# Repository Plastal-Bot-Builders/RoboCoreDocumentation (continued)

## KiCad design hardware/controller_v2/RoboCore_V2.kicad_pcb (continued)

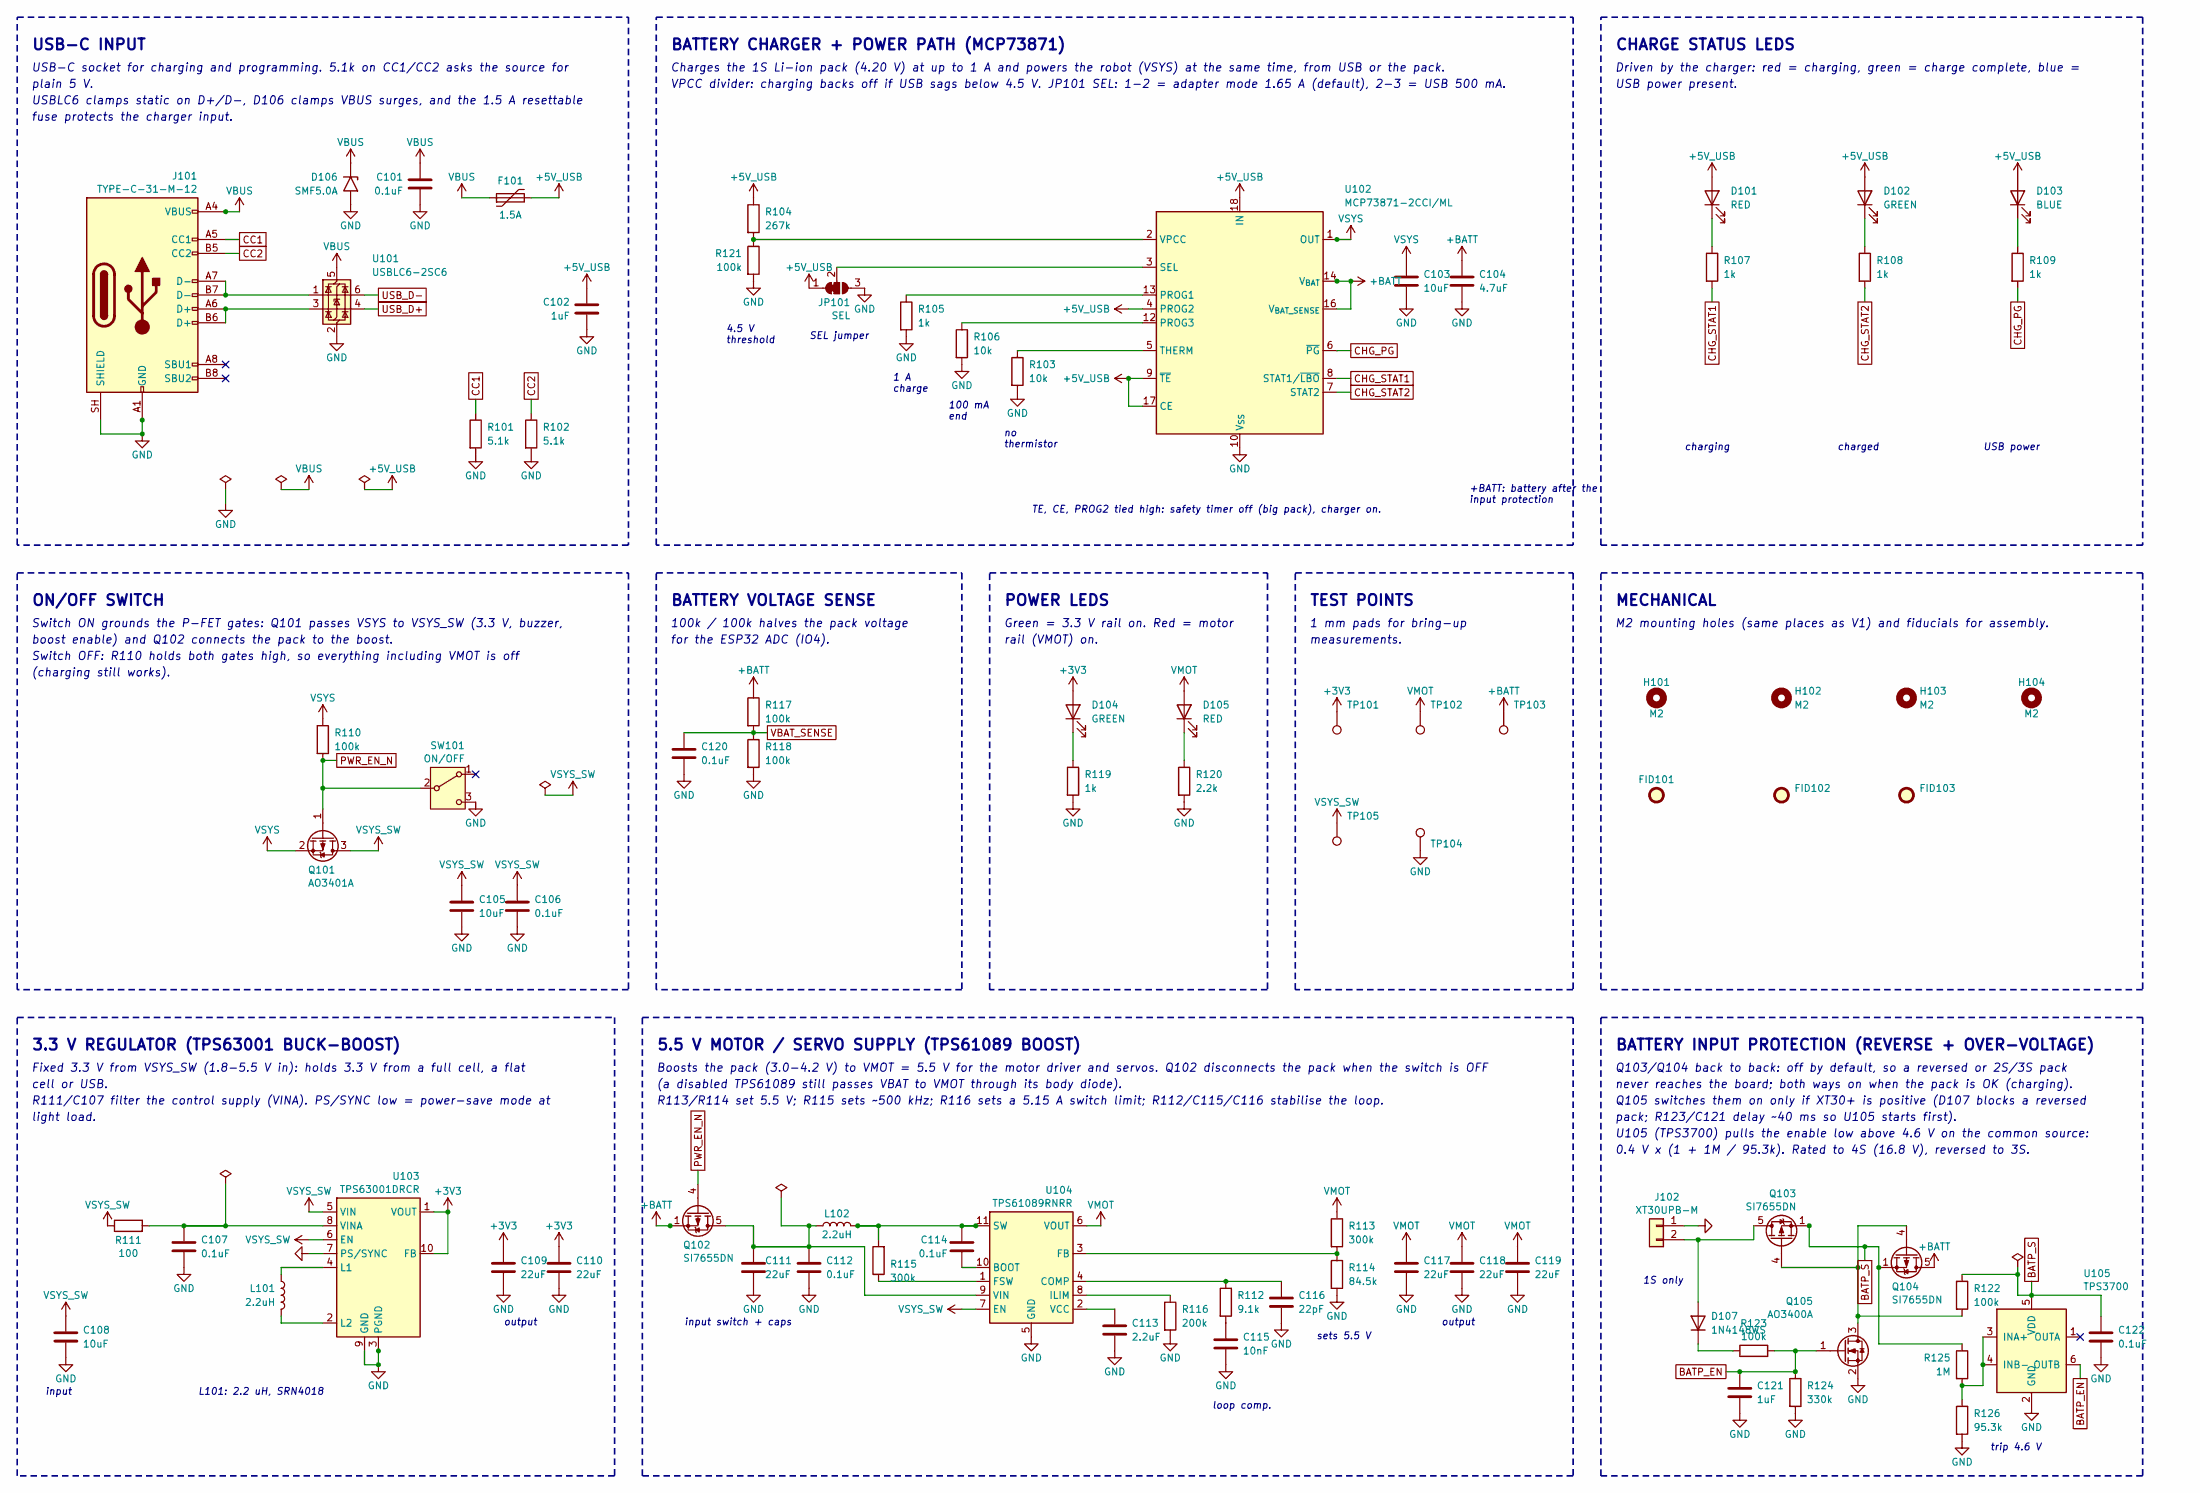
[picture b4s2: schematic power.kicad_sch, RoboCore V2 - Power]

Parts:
C101, C106, C107, C112, C114, C120, C122: 0.1uF; C_0402_1005Metric; LCSC C960916
C102: 1uF; C_0603_1608Metric; LCSC C5673
C103: 10uF; C_0603_1608Metric; LCSC C92487
C104: 4.7uF; C_0805_2012Metric; LCSC C1779
C105, C108: 10uF; C_0805_2012Metric; LCSC C1713
C109, C110: 22uF; C_0805_2012Metric; LCSC C45783
C111, C117, C118, C119: 22uF; C_1206_3216Metric; LCSC C12891
C113: 2.2uF; C_0603_1608Metric; LCSC C23630
C115: 10nF; C_0402_1005Metric; LCSC C15195
C116: 22pF; C_0402_1005Metric; LCSC C70464
C121: 1uF; C_0402_1005Metric; LCSC C16193167
D101, D105: RED; LED_0603_1608Metric; LCSC C125099
D102, D104: GREEN; LED_0603_1608Metric; LCSC C125098
D103: BLUE; LED_0603_1608Metric; LCSC C99290
D106: SMF5.0A; D_SMF; LCSC C151296
D107: 1N4148WS; D_SOD-323; LCSC C129905
F101: 1.5A; Fuse_1812_4532Metric; LCSC C78695
FID101, FID102, FID103: Fiducial; Fiducial_1mm_Mask2mm
H101, H102, H103, H104: M2; MountingHole_2.2mm_M2
J101: TYPE-C-31-M-12; USB_C_Receptacle_HRO_TYPE-C-31-M-12; LCSC C165948
J102: XT30UPB-M; AMASS_XT30UPB-M_1x02_P5.0mm_Vertical; LCSC C428721
JP101: SEL; SolderJumper-3_P1.3mm_Bridged12_RoundedPad1.0x1.5mm
L101: 2.2uH; L_Bourns-SRN4018; LCSC C913207
L102: 2.2uH; L_Bourns_SRP5030CA; LCSC C2046809
Q101: AO3401A; SOT-23; LCSC C15127
Q102, Q103, Q104: SI7655DN; Vishay_PowerPAK_1212-8_Single; LCSC C727830
Q105: AO3400A; SOT-23; LCSC C20917
R101, R102: 5.1k; R_0402_1005Metric; LCSC C25905
R103, R106: 10k; R_0402_1005Metric; LCSC C25744
R104: 267k; R_0402_1005Metric; LCSC C270622
R105, R107, R108, R109, R119: 1k; R_0402_1005Metric; LCSC C106235
R110, R117, R118, R121, R122, R123: 100k; R_0402_1005Metric; LCSC C25741
R111: 100; R_0402_1005Metric; LCSC C106232
R112: 9.1k; R_0402_1005Metric; LCSC C25926
R113, R115: 300k; R_0402_1005Metric; LCSC C25774
R114: 84.5k; R_0402_1005Metric; LCSC C26988
R116: 200k; R_0402_1005Metric; LCSC C25764
R120: 2.2k; R_0402_1005Metric; LCSC C25879
R124: 330k; R_0402_1005Metric; LCSC C25778
R125: 1M; R_0402_1005Metric; LCSC C26083
R126: 95.3k; R_0402_1005Metric; LCSC C26990
SW101: ON/OFF; SW_SPDT_CK_JS102011SAQN; LCSC C221660
TP101: +3V3; TestPoint_Pad_D1.0mm
TP102: VMOT; TestPoint_Pad_D1.0mm
TP103: +BATT; TestPoint_Pad_D1.0mm
TP104: GND; TestPoint_Pad_D1.0mm
TP105: VSYS_SW; TestPoint_Pad_D1.0mm
U101: USBLC6-2SC6; SOT-23-6; LCSC C7519
U102: MCP73871-2CCI/ML; QFN-20-1EP_4x4mm_P0.5mm_EP2.5x2.5mm_ThermalVias; LCSC C5121473
U103: TPS63001DRCR; Texas_DRC0010J_ThermalVias; LCSC C28060
U104: TPS61089RNRR; Texas_VQFN-RNR0011A-11; LCSC C165129
U105: TPS3700; TSOT-23-6; LCSC C33002

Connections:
+3V3: C109.1, C110.1, D104.2 (A), TP101.1, U103.1 (VOUT), U103.10 (FB); also elsewhere on the board
+5V_USB: C102.1, D101.2 (A), D102.2 (A), D103.2 (A), F101.2, JP101.1 (A), R104.1, U102.4 (PROG2), U102.9 (~TE), U102.17 (CE), U102.18 (IN), U102.19 (IN)
+BATT: C104.1, Q102.1 (S), Q102.2 (S), Q102.3 (S), Q104.5 (D), R117.1, TP103.1, U102.14 (V_{BAT}), U102.15 (V_{BAT}), U102.16 (V_{BAT_SENSE})
BATP_EN: C121.1, Q105.1 (G), R123.2, R124.1, U105.6 (OUTB)
BATP_S: C122.1, Q103.1 (S), Q103.2 (S), Q103.3 (S), Q104.1 (S), Q104.2 (S), Q104.3 (S), R122.1, R125.1, U105.5 (VDD)
CC1: J101.A5 (CC1), R101.1
CC2: J101.B5 (CC2), R102.1
CHG_PG: R109.2, U102.6 (~PG)
CHG_STAT1: R107.2, U102.8 (STAT1/~LBO)
CHG_STAT2: R108.2, U102.7 (STAT2)
GND: C101.2, C102.2, C103.2, C104.2, C105.2, C106.2, C107.2, C108.2, C109.2, C110.2, C111.2, C112.2, C113.2, C115.2, C116.2, C117.2, C118.2, C119.2, C120.2, C121.2, C122.2, D106.2 (A2), J101.A1 (GND), J101.A12 (GND), J101.B1 (GND), J101.B12 (GND), J101.SH (SHIELD), J102.1, JP101.3 (B), Q105.2 (S), R101.2, R102.2, R103.2, R105.2, R106.2, R114.2, R116.2, R118.2, R119.2, R120.2, R121.2, R124.2, R126.2, SW101.3 (C), TP104.1, U101.2 (GND), U102.10 (V_{SS}), U102.11 (V_{SS}), U102.21 (V_{SS}), U103.3 (PGND), U103.7 (PS/SYNC), U103.9 (GND), U103.11 (PGND), U104.5 (GND), U105.2 (GND); also elsewhere on the board
unnamed: C115.1, R112.2
unnamed: D101.1 (K), R107.1
unnamed: D102.1 (K), R108.1
unnamed: D103.1 (K), R109.1
unnamed: D104.1 (K), R119.1
unnamed: D105.1 (K), R120.1
unnamed: D107.2 (A), J102.2, Q103.5 (D)
unnamed: D107.1 (K), R123.1
unnamed: J101.A6 (D+), J101.B6 (D+), U101.3 (I/O2)
unnamed: J101.A7 (D-), J101.B7 (D-), U101.1 (I/O1)
unnamed: JP101.2 (C), U102.3 (SEL)
unnamed: C111.1, C112.1, L102.1, Q102.5 (D), U104.9 (VIN)
unnamed: Q103.4 (G), Q104.4 (G), Q105.3 (D), R122.2
unnamed: R105.1, U102.13 (PROG1)
unnamed: R106.1, U102.12 (PROG3)
unnamed: R103.1, U102.5 (THERM)
unnamed: R104.2, R121.1, U102.2 (VPCC)
unnamed: L101.1, U103.4 (L1)
unnamed: L101.2, U103.2 (L2)
unnamed: C107.1, R111.2, U103.8 (VINA)
unnamed: C114.1, U104.10 (BOOT)
unnamed: C116.1, R112.1, U104.4 (COMP)
unnamed: R113.2, R114.1, U104.3 (FB)
unnamed: R115.1, U104.1 (FSW)
unnamed: R116.1, U104.8 (ILIM)
unnamed: C114.2, L102.2, R115.2, U104.11 (SW)
unnamed: C113.1, U104.2 (VCC)
unnamed: R125.2, R126.1, U105.3 (INA+), U105.4 (INB-)
PWR_EN_N: Q101.1 (G), Q102.4 (G), R110.2, SW101.2 (B)
USB_D+: U101.4 (I/O2); also elsewhere on the board
USB_D-: U101.6 (I/O1); also elsewhere on the board
VBAT_SENSE: C120.1, R117.2, R118.1; also elsewhere on the board
VBUS: C101.1, D106.1 (A1), F101.1, J101.A4 (VBUS), J101.A9 (VBUS), J101.B4 (VBUS), J101.B9 (VBUS), U101.5 (VBUS)
VMOT: C117.1, C118.1, C119.1, D105.2 (A), R113.1, TP102.1, U104.6 (VOUT); also elsewhere on the board
VSYS: C103.1, Q101.2 (S), R110.1, U102.1 (OUT), U102.20 (OUT)
VSYS_SW: C105.1, C106.1, C108.1, Q101.3 (D), R111.1, TP105.1, U103.5 (VIN), U103.6 (EN), U104.7 (EN); also elsewhere on the board

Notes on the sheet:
USB-C INPUT
USB-C socket for charging and programming. 5.1k on CC1/CC2 asks the source for
plain 5 V.
USBLC6 clamps static on D+/D-, D106 clamps VBUS surges, and the 1.5 A resettable
fuse protects the charger input.
BATTERY CHARGER + POWER PATH (MCP73871)
Charges the 1S Li-ion pack (4.20 V) at up to 1 A and powers the robot (VSYS) at the same time, from USB or the pack.
VPCC divider: charging backs off if USB sags below 4.5 V. JP101 SEL: 1-2 = adapter mode 1.65 A (default), 2-3 = USB 500 mA.
4.5 V
threshold
SEL jumper
1 A
charge
100 mA
end
thermistor
TE, CE, PROG2 tied high: safety timer off (big pack), charger on.
+BATT: battery after the
input protection
CHARGE STATUS LEDS
Driven by the charger: red = charging, green = charge complete, blue =
USB power present.
charging
charged
USB power
ON/OFF SWITCH
Switch ON grounds the P-FET gates: Q101 passes VSYS to VSYS_SW (3.3 V, buzzer,
boost enable) and Q102 connects the pack to the boost.
Switch OFF: R110 holds both gates high, so everything including VMOT is off
(charging still works).
BATTERY VOLTAGE SENSE
100k / 100k halves the pack voltage
for the ESP32 ADC (IO4).
POWER LEDS
Green = 3.3 V rail on. Red = motor
rail (VMOT) on.
TEST POINTS
1 mm pads for bring-up
measurements.
MECHANICAL

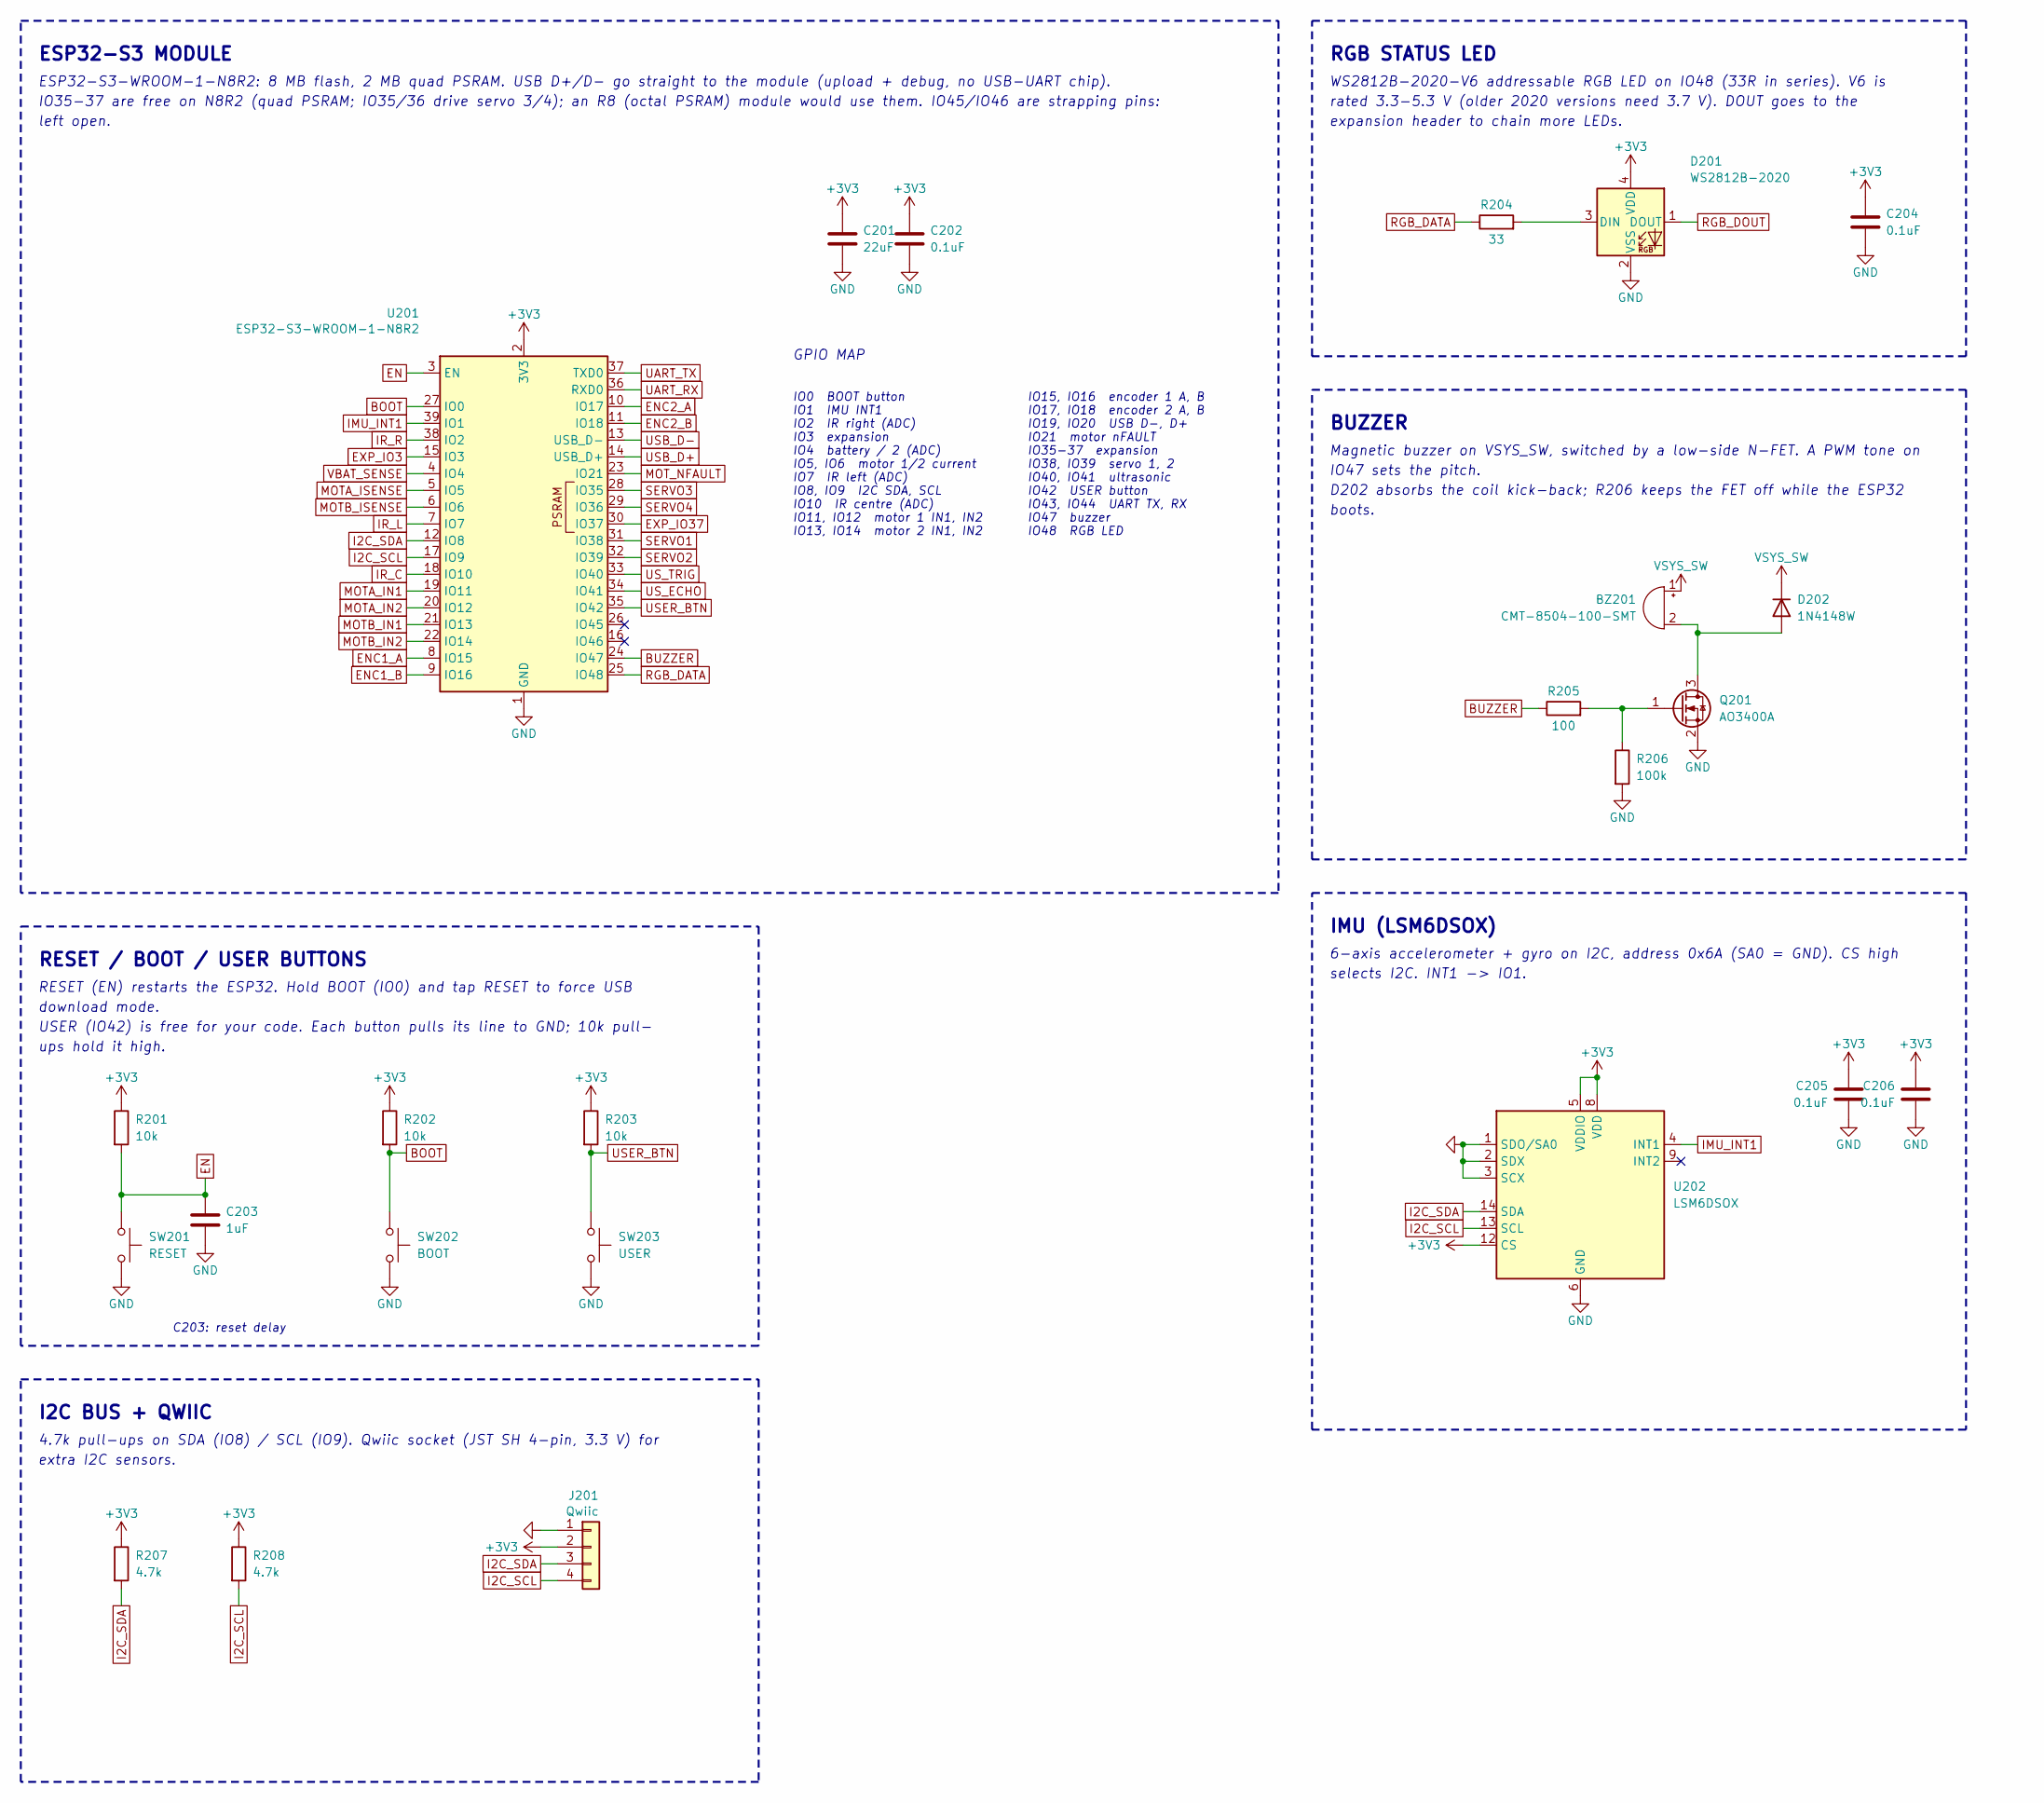
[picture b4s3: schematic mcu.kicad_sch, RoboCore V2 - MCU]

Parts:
BZ201: CMT-8504-100-SMT; MagneticBuzzer_CUI_CMT-8504-100-SMT; LCSC C22359707
C201: 22uF; C_0805_2012Metric; LCSC C45783
C202, C204, C205, C206: 0.1uF; C_0402_1005Metric; LCSC C960916
C203: 1uF; C_0402_1005Metric; LCSC C16193167
D201: WS2812B-2020; LED_WS2812B-2020_PLCC4_2.0x2.0mm; LCSC C52917434
D202: 1N4148W; D_SOD-123; LCSC C83528
J201: Qwiic; JST_SH_BM04B-SRSS-TB_1x04-1MP_P1.00mm_Vertical; LCSC C160390
Q201: AO3400A; SOT-23; LCSC C20917
R201, R202, R203: 10k; R_0402_1005Metric; LCSC C25744
R204: 33; R_0402_1005Metric; LCSC C138002
R205: 100; R_0402_1005Metric; LCSC C106232
R206: 100k; R_0402_1005Metric; LCSC C25741
R207, R208: 4.7k; R_0402_1005Metric; LCSC C25900
SW201: RESET; SW_SPST_SKQG_WithoutStem; LCSC C116647
SW202: BOOT; SW_SPST_SKQG_WithoutStem; LCSC C116647
SW203: USER; SW_SPST_SKQG_WithoutStem; LCSC C116647
U201: ESP32-S3-WROOM-1-N8R2; ESP32-S3-WROOM-1; LCSC C2913204
U202: LSM6DSOX; LGA-14_3x2.5mm_P0.5mm_LayoutBorder3x4y; LCSC C481766

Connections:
+3V3: C201.1, C202.1, C204.1, C205.1, C206.1, D201.4 (VDD), J201.2, R201.1, R202.1, R203.1, R207.1, R208.1, U201.2 (3V3), U202.5 (VDDIO), U202.8 (VDD), U202.12 (CS); also elsewhere on the board
BOOT: R202.2, SW202.1, U201.27 (IO0)
BUZZER: R205.1, U201.24 (IO47); also elsewhere on the board
EN: C203.1, R201.2, SW201.1, U201.3 (EN); also elsewhere on the board
ENC1_A: U201.8 (IO15); also elsewhere on the board
ENC1_B: U201.9 (IO16); also elsewhere on the board
ENC2_A: U201.10 (IO17); also elsewhere on the board
ENC2_B: U201.11 (IO18); also elsewhere on the board
EXP_IO3: U201.15 (IO3); also elsewhere on the board
EXP_IO37: U201.30 (IO37); also elsewhere on the board
GND: C201.2, C202.2, C203.2, C204.2, C205.2, C206.2, D201.2 (VSS), J201.1, Q201.2 (S), R206.2, SW201.2, SW202.2, SW203.2, U201.1 (GND), U201.40 (GND), U201.41 (GND), U202.1 (SDO/SA0), U202.2 (SDX), U202.3 (SCX), U202.6 (GND), U202.7 (GND); also elsewhere on the board
I2C_SCL: J201.4, R208.2, U201.17 (IO9), U202.13 (SCL); also elsewhere on the board
I2C_SDA: J201.3, R207.2, U201.12 (IO8), U202.14 (SDA); also elsewhere on the board
IMU_INT1: U201.39 (IO1), U202.4 (INT1); also elsewhere on the board
IR_C: U201.18 (IO10); also elsewhere on the board
IR_L: U201.7 (IO7); also elsewhere on the board
IR_R: U201.38 (IO2); also elsewhere on the board
MOTA_IN1: U201.19 (IO11); also elsewhere on the board
MOTA_IN2: U201.20 (IO12); also elsewhere on the board
MOTA_ISENSE: U201.5 (IO5); also elsewhere on the board
MOTB_IN1: U201.21 (IO13); also elsewhere on the board
MOTB_IN2: U201.22 (IO14); also elsewhere on the board
MOTB_ISENSE: U201.6 (IO6); also elsewhere on the board
MOT_NFAULT: U201.23 (IO21); also elsewhere on the board
unnamed: BZ201.2 (-), D202.2 (A), Q201.3 (D)
unnamed: D201.3 (DIN), R204.2
unnamed: Q201.1 (G), R205.2, R206.1
RGB_DATA: R204.1, U201.25 (IO48)
RGB_DOUT: D201.1 (DOUT); also elsewhere on the board
SERVO1: U201.31 (IO38); also elsewhere on the board
SERVO2: U201.32 (IO39); also elsewhere on the board
SERVO3: U201.28 (IO35); also elsewhere on the board
SERVO4: U201.29 (IO36); also elsewhere on the board
UART_RX: U201.36 (RXD0); also elsewhere on the board
UART_TX: U201.37 (TXD0); also elsewhere on the board
USB_D+: U201.14 (USB_D+); also elsewhere on the board
USB_D-: U201.13 (USB_D-); also elsewhere on the board
USER_BTN: R203.2, SW203.1, U201.35 (IO42); also elsewhere on the board
US_ECHO: U201.34 (IO41); also elsewhere on the board
US_TRIG: U201.33 (IO40); also elsewhere on the board
VBAT_SENSE: U201.4 (IO4); also elsewhere on the board
VSYS_SW: BZ201.1 (+), D202.1 (K); also elsewhere on the board

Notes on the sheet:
ESP32-S3 MODULE
ESP32-S3-WROOM-1-N8R2: 8 MB flash, 2 MB quad PSRAM. USB D+/D- go straight to the module (upload + debug, no USB-UART chip).
IO35-37 are free on N8R2 (quad PSRAM; IO35/36 drive servo 3/4); an R8 (octal PSRAM) module would use them. IO45/IO46 are strapping pins:
left open.
GPIO MAP
IO0 BOOT button
IO1 IMU INT1
IO2 IR right (ADC)
IO3 expansion
IO4 battery / 2 (ADC)
IO5, IO6 motor 1/2 current
IO7 IR left (ADC)
IO8, IO9 I2C SDA, SCL
IO10 IR centre (ADC)
IO11, IO12 motor 1 IN1, IN2
IO13, IO14 motor 2 IN1, IN2
IO15, IO16 encoder 1 A, B
IO17, IO18 encoder 2 A, B
IO19, IO20 USB D-, D+
IO21 motor nFAULT
IO35-37 expansion
IO38, IO39 servo 1, 2
IO40, IO41 ultrasonic
IO42 USER button
IO43, IO44 UART TX, RX
IO47 buzzer
IO48 RGB LED
RESET / BOOT / USER BUTTONS
RESET (EN) restarts the ESP32. Hold BOOT (IO0) and tap RESET to force USB
download mode.
USER (IO42) is free for your code. Each button pulls its line to GND; 10k pull-
ups hold it high.
C203: reset delay
I2C BUS + QWIIC
4.7k pull-ups on SDA (IO8) / SCL (IO9). Qwiic socket (JST SH 4-pin, 3.3 V) for
extra I2C sensors.
RGB STATUS LED
WS2812B-2020-V6 addressable RGB LED on IO48 (33R in series). V6 is
rated 3.3-5.3 V (older 2020 versions need 3.7 V). DOUT goes to the
expansion header to chain more LEDs.

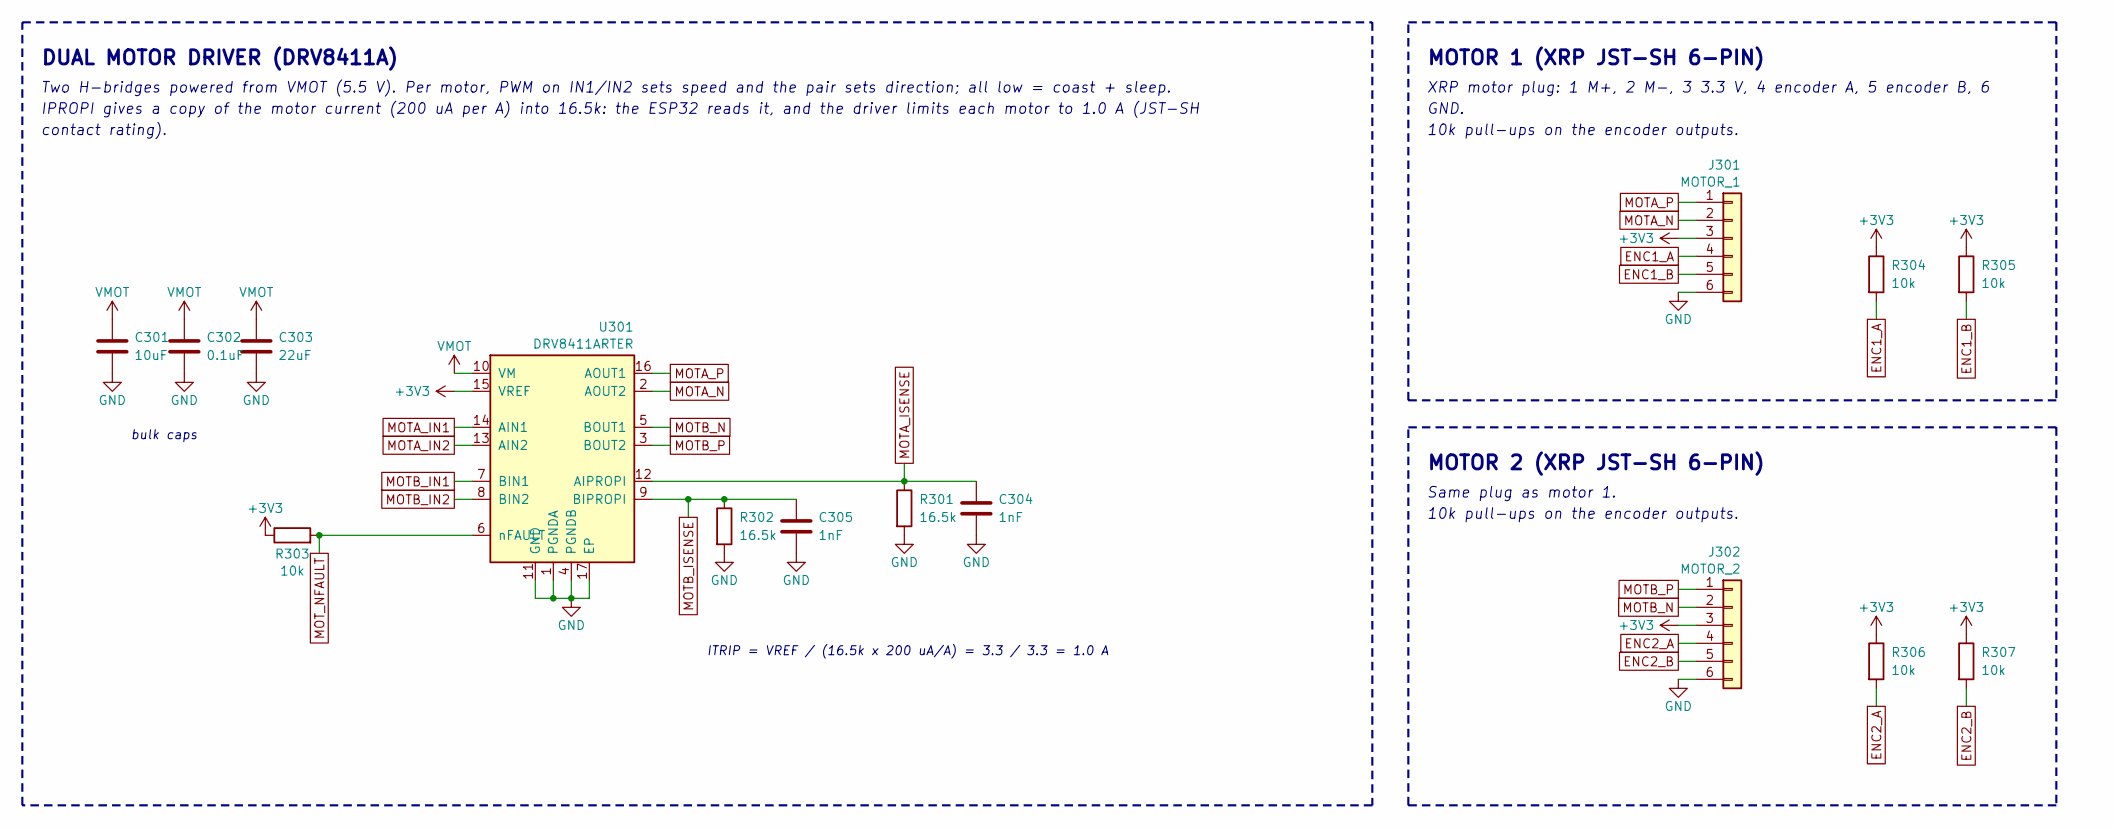
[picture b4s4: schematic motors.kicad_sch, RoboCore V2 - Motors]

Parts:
C301: 10uF; C_0805_2012Metric; LCSC C1713
C302: 0.1uF; C_0402_1005Metric; LCSC C960916
C303: 22uF; C_1206_3216Metric; LCSC C12891
C304, C305: 1nF; C_0402_1005Metric; LCSC C14442
J301: MOTOR_1; JST_SH_BM06B-SRSS-TB_1x06-1MP_P1.00mm_Vertical; LCSC C160392
J302: MOTOR_2; JST_SH_BM06B-SRSS-TB_1x06-1MP_P1.00mm_Vertical; LCSC C160392
R301, R302: 16.5k; R_0402_1005Metric; LCSC C25857
R303, R304, R305, R306, R307: 10k; R_0402_1005Metric; LCSC C25744
U301: DRV8411ARTER; WQFN-16-1EP_3x3mm_P0.5mm_EP1.68x1.68mm_ThermalVias; LCSC C18816315

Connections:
+3V3: J301.3, J302.3, R303.1, R304.1, R305.1, R306.1, R307.1, U301.15 (VREF); also elsewhere on the board
ENC1_A: J301.4, R304.2; also elsewhere on the board
ENC1_B: J301.5, R305.2; also elsewhere on the board
ENC2_A: J302.4, R306.2; also elsewhere on the board
ENC2_B: J302.5, R307.2; also elsewhere on the board
GND: C301.2, C302.2, C303.2, C304.2, C305.2, J301.6, J302.6, R301.2, R302.2, U301.1 (PGNDA), U301.4 (PGNDB), U301.11 (GND), U301.17 (EP); also elsewhere on the board
MOTA_IN1: U301.14 (AIN1); also elsewhere on the board
MOTA_IN2: U301.13 (AIN2); also elsewhere on the board
MOTA_ISENSE: C304.1, R301.1, U301.12 (AIPROPI); also elsewhere on the board
MOTA_N: J301.2, U301.2 (AOUT2)
MOTA_P: J301.1, U301.16 (AOUT1)
MOTB_IN1: U301.7 (BIN1); also elsewhere on the board
MOTB_IN2: U301.8 (BIN2); also elsewhere on the board
MOTB_ISENSE: C305.1, R302.1, U301.9 (BIPROPI); also elsewhere on the board
MOTB_N: J302.2, U301.5 (BOUT1)
MOTB_P: J302.1, U301.3 (BOUT2)
MOT_NFAULT: R303.2, U301.6 (nFAULT); also elsewhere on the board
VMOT: C301.1, C302.1, C303.1, U301.10 (VM); also elsewhere on the board

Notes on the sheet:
DUAL MOTOR DRIVER (DRV8411A)
Two H-bridges powered from VMOT (5.5 V). Per motor, PWM on IN1/IN2 sets speed and the pair sets direction; all low = coast + sleep.
IPROPI gives a copy of the motor current (200 uA per A) into 16.5k: the ESP32 reads it, and the driver limits each motor to 1.0 A (JST-SH
contact rating).
ITRIP = VREF / (16.5k x 200 uA/A) = 3.3 / 3.3 = 1.0 A
bulk caps
MOTOR 1 (XRP JST-SH 6-PIN)
XRP motor plug: 1 M+, 2 M-, 3 3.3 V, 4 encoder A, 5 encoder B, 6
GND.
10k pull-ups on the encoder outputs.
MOTOR 2 (XRP JST-SH 6-PIN)
Same plug as motor 1.

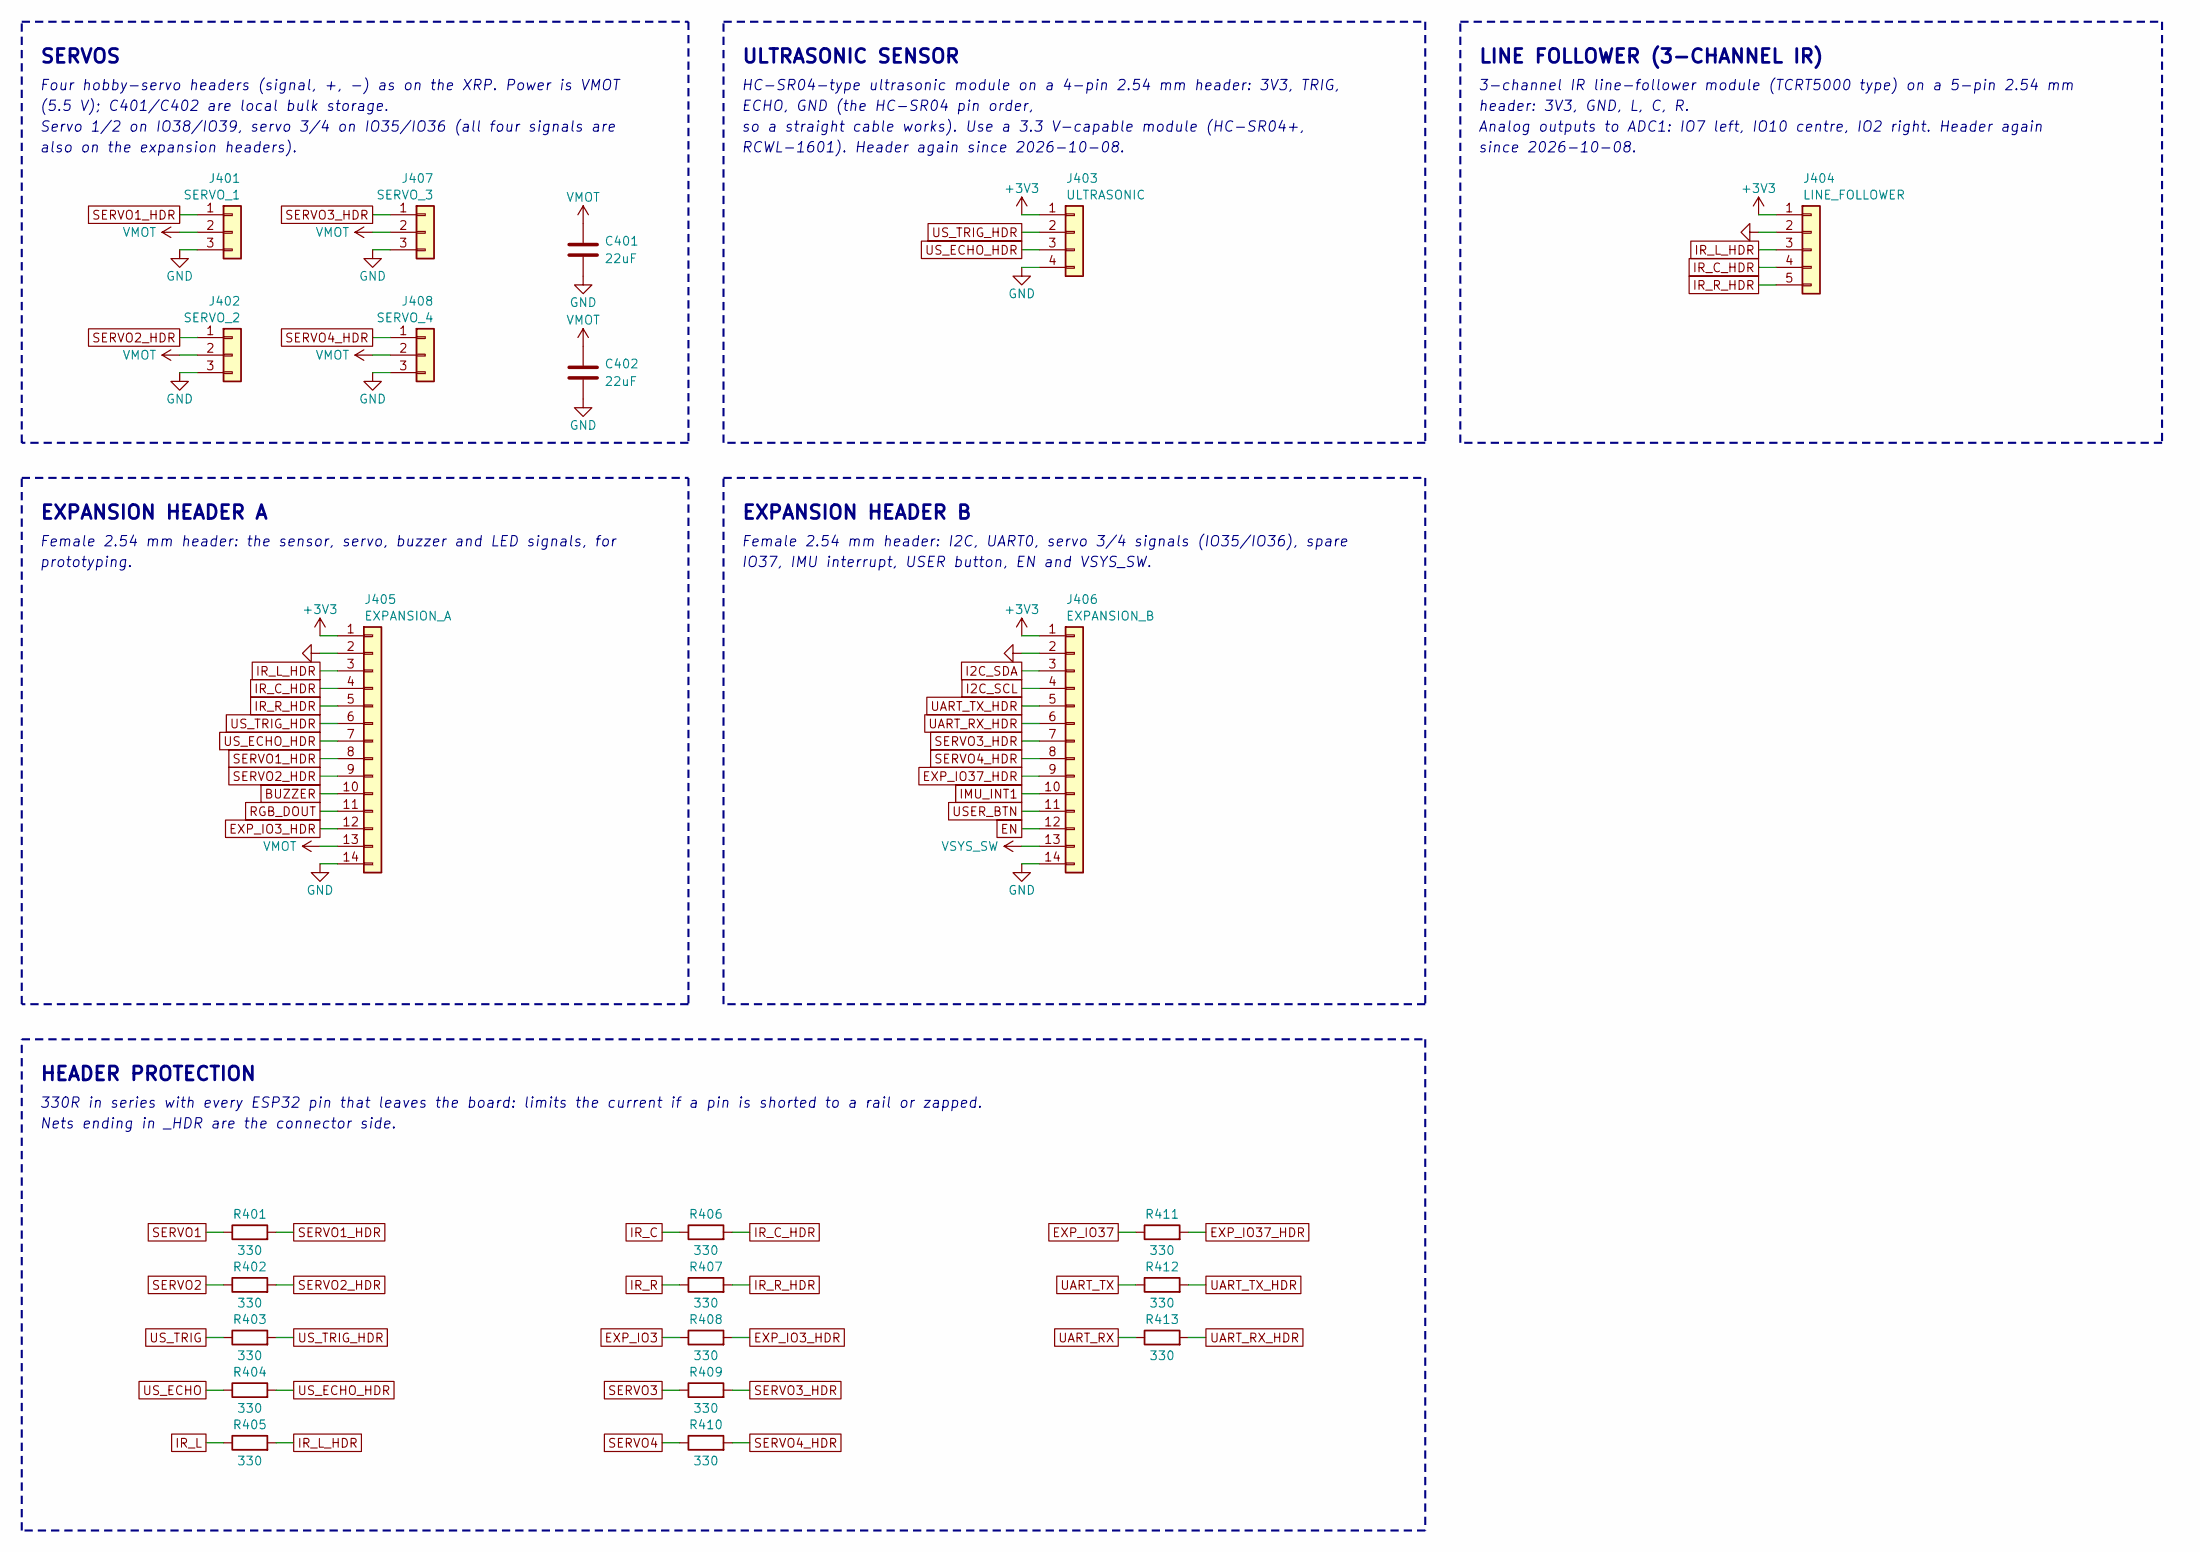
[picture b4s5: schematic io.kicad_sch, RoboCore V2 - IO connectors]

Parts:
C401, C402: 22uF; C_1206_3216Metric; LCSC C12891
J401: SERVO_1; PinHeader_1x03_P2.54mm_Vertical; LCSC C52016391
J402: SERVO_2; PinHeader_1x03_P2.54mm_Vertical; LCSC C52016391
J403: ULTRASONIC; PinHeader_1x04_P2.54mm_Vertical; LCSC C52016392
J404: LINE_FOLLOWER; PinHeader_1x05_P2.54mm_Vertical; LCSC C27985190
J405: EXPANSION_A; PinSocket_1x14_P2.54mm_Vertical; LCSC C22373900
J406: EXPANSION_B; PinSocket_1x14_P2.54mm_Vertical; LCSC C22373900
J407: SERVO_3; PinHeader_1x03_P2.54mm_Vertical; LCSC C52016391
J408: SERVO_4; PinHeader_1x03_P2.54mm_Vertical; LCSC C52016391
R401, R402, R403, R404, R405, R406, R407, R408, R409, R410, R411, R412, R413: 330; R_0402_1005Metric; LCSC C25104

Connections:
+3V3: J403.1, J404.1, J405.1, J406.1; also elsewhere on the board
BUZZER: J405.10; also elsewhere on the board
EN: J406.12; also elsewhere on the board
EXP_IO3: R408.1; also elsewhere on the board
EXP_IO3_HDR: J405.12, R408.2
EXP_IO37: R411.1; also elsewhere on the board
EXP_IO37_HDR: J406.9, R411.2
GND: C401.2, C402.2, J401.3, J402.3, J403.4, J404.2, J405.2, J405.14, J406.2, J406.14, J407.3, J408.3; also elsewhere on the board
I2C_SCL: J406.4; also elsewhere on the board
I2C_SDA: J406.3; also elsewhere on the board
IMU_INT1: J406.10; also elsewhere on the board
IR_C: R406.1; also elsewhere on the board
IR_C_HDR: J404.4, J405.4, R406.2
IR_L: R405.1; also elsewhere on the board
IR_L_HDR: J404.3, J405.3, R405.2
IR_R: R407.1; also elsewhere on the board
IR_R_HDR: J404.5, J405.5, R407.2
RGB_DOUT: J405.11; also elsewhere on the board
SERVO1: R401.1; also elsewhere on the board
SERVO1_HDR: J401.1, J405.8, R401.2
SERVO2: R402.1; also elsewhere on the board
SERVO2_HDR: J402.1, J405.9, R402.2
SERVO3: R409.1; also elsewhere on the board
SERVO3_HDR: J406.7, J407.1, R409.2
SERVO4: R410.1; also elsewhere on the board
SERVO4_HDR: J406.8, J408.1, R410.2
UART_RX: R413.1; also elsewhere on the board
UART_RX_HDR: J406.6, R413.2
UART_TX: R412.1; also elsewhere on the board
UART_TX_HDR: J406.5, R412.2
USER_BTN: J406.11; also elsewhere on the board
US_ECHO: R404.1; also elsewhere on the board
US_ECHO_HDR: J403.3, J405.7, R404.2
US_TRIG: R403.1; also elsewhere on the board
US_TRIG_HDR: J403.2, J405.6, R403.2
VMOT: C401.1, C402.1, J401.2, J402.2, J405.13, J407.2, J408.2; also elsewhere on the board
VSYS_SW: J406.13; also elsewhere on the board

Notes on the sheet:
SERVOS
Four hobby-servo headers (signal, +, -) as on the XRP. Power is VMOT
(5.5 V); C401/C402 are local bulk storage.
Servo 1/2 on IO38/IO39, servo 3/4 on IO35/IO36 (all four signals are
also on the expansion headers).
ULTRASONIC SENSOR
HC-SR04-type ultrasonic module on a 4-pin 2.54 mm header: 3V3, TRIG,
ECHO, GND (the HC-SR04 pin order,
so a straight cable works). Use a 3.3 V-capable module (HC-SR04+,
RCWL-1601). Header again since 2026-10-08.
LINE FOLLOWER (3-CHANNEL IR)
3-channel IR line-follower module (TCRT5000 type) on a 5-pin 2.54 mm
header: 3V3, GND, L, C, R.
Analog outputs to ADC1: IO7 left, IO10 centre, IO2 right. Header again
since 2026-10-08.
EXPANSION HEADER A
Female 2.54 mm header: the sensor, servo, buzzer and LED signals, for
prototyping.
EXPANSION HEADER B
Female 2.54 mm header: I2C, UART0, servo 3/4 signals (IO35/IO36), spare
IO37, IMU interrupt, USER button, EN and VSYS_SW.
HEADER PROTECTION
330R in series with every ESP32 pin that leaves the board: limits the current if a pin is shorted to a rail or zapped.
Nets ending in _HDR are the connector side.
